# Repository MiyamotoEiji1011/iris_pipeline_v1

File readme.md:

# iris pipeline v1
空調設備管理デバイス
各空調機（エアコン）の温度を計測し、空調設備の電力効率向上を目的として、必要に応じてミストを噴射し、銅管温度を低下させるデバイスです。
温度センサから取得した測定値をもとに電磁弁を自動制御し、設定された温度条件に応じてミストの噴射・停止を行います。

※温度センサについて
各空調機に2台のセンサを使用する。
銅管と空気の吸気部分の2か所に配置して温度を測定する。
電磁弁の制御に使用する値はwebアプリ側で切り替えれるようにする。

# 配線
## 温度センサ(DS18B20)
GPIO04=sensor_A1,sensor_A2
GPIO05=sensor_B1,sensor_B2
GPIO06=sensor_C1,sensor_C2

GPIO12=sensor_D1,sensor_D2
GPIO13=sensor_E1,sensor_E2
GPIO16=sensor_F1,sensor_F2

GPIO17=sensor_G1,sensor_G2
GPIO18=sensor_H1,sensor_H2
GPIO19=sensor_I1,sensor_I2

GPIO20=sensor_J1,sensor_J2
GPIO21=sensor_K1,sensor_K2
GPIO26=sensor_L1,sensor_L2
## 電磁バルブ(12V)
リレーモジュールに接続(8つ)
## リレーモジュール(リレー*8)
GPIO07=relay_A
GPIO08=relay_B
GPIO09=relay_C
GPIO10=relay_D
GPIO11=relay_E
GPIO22=relay_F
GPIO23=relay_G
GPIO24=relay_H
## LED
GPIO25=DAEMON_LED
GPIO27=API_LED
GPIO14=NETWORK_LED
## SW
GPIO15=Reset_SW

# webアプリ
githubPagesをもちいて、ラズパイ側のッデータの受け取りや設定の書き換えなどを行う。APIを使用してユーザーが任意のタイミングでリクエストができるようにする。常時通信は行わない。

# コード
## main
tools,systemを使用して制御を行う。

## tools
・read_temp_sensor.py
read_temp_sensor(GPIO)->list(float)
任意のGPIOの温度センサーの値を取得可能できる数取得し返す。
・write_relay_module.py
write_relay_module(GPIO,bool)->bool()
リレーモジュールのGPIOのHIGH/LOWを切り替える
・write_temp_date.py
write_temp_date()->xlsx
指定の形式で温度データを渡すことでエクセルファイル追加保存する。また、エクセルファイルの新規作成などの関数もある。
・write_log.py
write_log()->txt
各、処理のログなどをすべて時間とともに保存する。
最大1000行までのログを記載し、超える場合は古い記録と入れ替える。

## api
未定

## system
・read_network.py
ネットワーク接続状態を確認する。
・read_api.py
外部アプリからの接続や編集を管理
・read_reset_switch.py
デーモンを終了し、システムを再起動
・read_system.py
OSの状態を管理

## config
・attach_pin.json
各GPIOのピン設定などを名前付けして定義づける。main.pyは起動時にこのファイルから読み込んだPINを使用して制御を行う。また、温度センサーの識別IDも記載。
・date_config.json
データの読み取り間隔などデータの記録に関する定義を保存するファイル。
・process_config.json
各電磁弁の開閉温度の設定、各空調機の制御で銅管温度と吸気温度のどちらを設定しているのかを保存しているファイル。
・config
　githubなどのアカウント関係に紐づく値を管理

# raspi
cd ~/iris_pipeline_v1/raspi
git pull
source .venv/bin/activate
pip install -r requirements.txt

## git
cd ~/iris_pipeline_v1
git add .
git commit -m "update raspi code"
git push

## デーモン（systemd）

### 初回登録
```bash
sudo cp ~/iris_pipeline_v1/raspi/iris_pipeline.service /etc/systemd/system/
sudo systemctl daemon-reload
sudo systemctl enable iris_pipeline
sudo systemctl start iris_pipeline
```

### 状態確認
```bash
sudo systemctl status iris_pipeline
```

### ログ確認
```bash
journalctl -u iris_pipeline -f
```

### 停止 / 起動 / 再起動
```bash
sudo systemctl stop iris_pipeline
sudo systemctl start iris_pipeline
sudo systemctl restart iris_pipeline
```

### 自動起動の無効化
```bash
sudo systemctl disable iris_pipeline
```

### コード更新後の反映手順
```bash
cd ~/iris_pipeline_v1
git pull
sudo systemctl restart iris_pipeline
```

## システム監視デーモン（iris_system）

ネットワーク状態 LED と リセット SW を管理する独立デーモン。

### sudo reboot の許可設定（初回のみ）
```bash
sudo visudo
```
以下の行を末尾に追加して保存：
```
pi ALL=(ALL) NOPASSWD: /sbin/reboot
```

### 初回登録
```bash
sudo cp ~/iris_pipeline_v1/raspi/iris_system.service /etc/systemd/system/
sudo systemctl daemon-reload
sudo systemctl enable iris_system
sudo systemctl start iris_system
```

### 状態確認 / ログ
```bash
sudo systemctl status iris_system
journalctl -u iris_system -f
```

### 停止 / 起動 / 再起動
```bash
sudo systemctl stop iris_system
sudo systemctl start iris_system
sudo systemctl restart iris_system
```

### コード更新後の反映手順
```bash
cd ~/iris_pipeline_v1
git pull
sudo systemctl restart iris_system
```

# webapp
https://miyamotoeiji1011.github.io/iris_pipeline_v1/

# Tailscale
IPの確認
tailscale ip -4

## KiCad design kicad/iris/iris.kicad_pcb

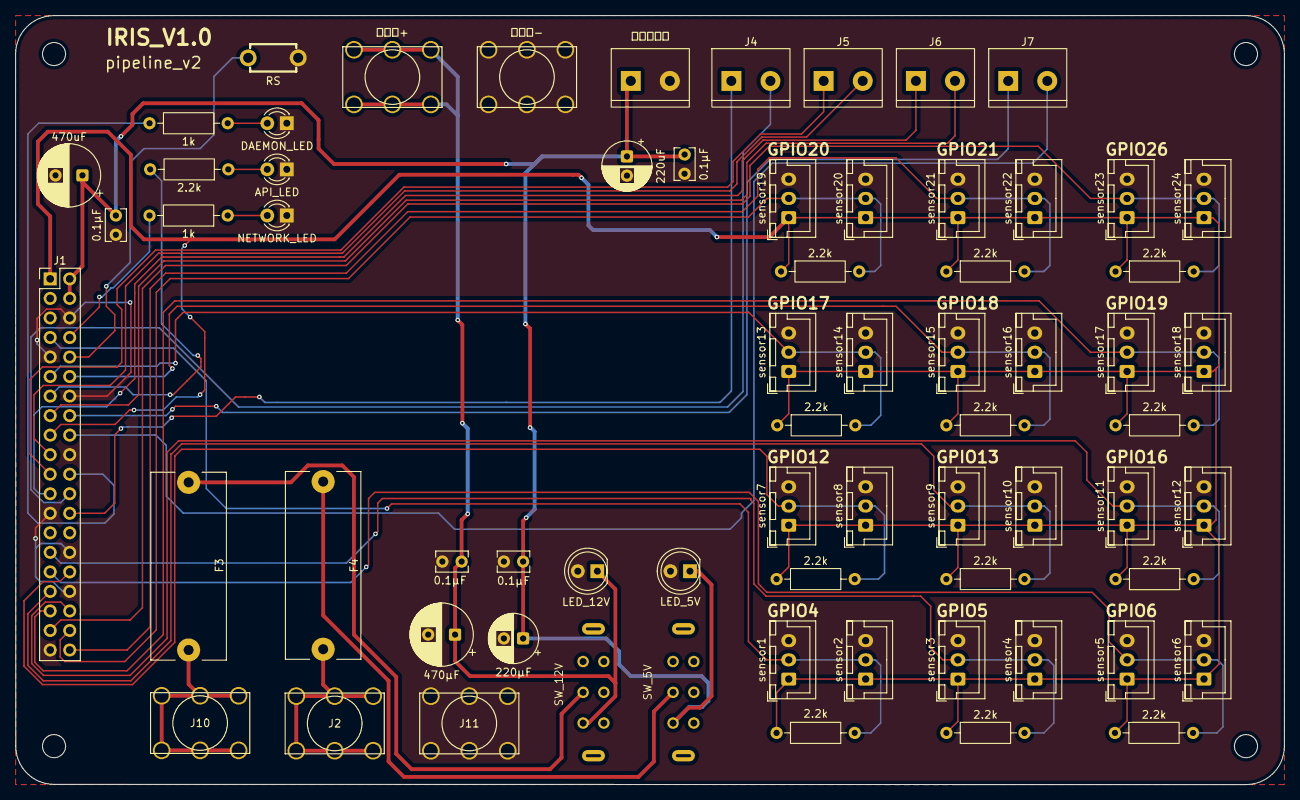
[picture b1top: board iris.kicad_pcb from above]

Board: 2 copper layers, 165.0 x 100.0 mm, 68 parts (0 on the bottom side), 35 nets.

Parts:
0.1µF, 0.1µF#2, 0.1µF#3, 0.1µF#4: 0.1µF; C_Rect_L4.0mm_W2.5mm_P2.50mm
1k, 1k#2: 1k; R_Axial_DIN0207_L6.3mm_D2.5mm_P10.16mm_Horizontal
2.2k, 2.2k#2, 2.2k#3, 2.2k#4, 2.2k#5, 2.2k#6, 2.2k#7, 2.2k#8, 2.2k#9, 2.2k#10, 2.2k#11, 2.2k#12, 2.2k#13: 2.2k; R_Axial_DIN0207_L6.3mm_D2.5mm_P10.16mm_Horizontal
220uF: 220uF; CP_Radial_D6.3mm_P2.50mm
220µF: 220µF; CP_Radial_D6.3mm_P2.50mm
470uF: 470uF; CP_Radial_D8.0mm_P3.50mm
470µF: 470µF; CP_Radial_D8.0mm_P3.50mm
API_LED: API_LED; LED_D3.0mm
DAEMON_LED: DAEMON_LED; LED_D3.0mm
F3, F4: Fuse; Fuseholder_Cylinder-5x20mm_MF-563
J1: Conn_02x20_Odd_Even; PinHeader_2x20_P2.54mm_Vertical
J2: 電源5V; PCB-20(632)F
J4, J5, J6, J7: 信号ターミナル; TerminalBlock_Alphaplus_TB111-2-2-E-1-1_1x02_P5.08_Horizont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
J10: 電源12V; PCB-20(632)F
J11: 電源GND; PCB-20(632)F
LED_5V: OSG8NU5B64A-5V; LED_D5.0mm
LED_12V: OSG8NU5B64A-12V; LED_D5.0mm
NETWORK_LED: NETWORK_LED; LED_D3.0mm
RS: SW_Push; sw_TVBP06-B043CB-B
SW_5V, SW_12V: SW_DPDT_x2; SS22F06G5-G
sensor1, sensor2, sensor3, sensor4, sensor5, sensor6, sensor7, sensor8, sensor9, sensor10, sensor11, sensor12, sensor13, sensor14, sensor15, sensor16, sensor17, sensor18, sensor19, sensor20, sensor21, sensor22, sensor23, sensor24: B3B-XH-A(LF)(SN); JST_XH_B3B-XH-A_1x03_P2.50mm_Vertical
リレー電源: リレー電源ターミナル; TerminalBlock_Alphaplus_TB111-2-2-E-1-1_1x02_P5.08_Horizont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
電磁弁+: 電磁弁+; PCB-20(632)F
電磁弁-: 電磁弁-; PCB-20(632)F

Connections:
+3V3: 2.2k.1, 2.2k#2.1, 2.2k#3.1, 2.2k#4.1, 2.2k#6.1, 2.2k#7.1, 2.2k#8.1, 2.2k#9.1, 2.2k#10.1, 2.2k#11.1, 2.2k#12.1, 2.2k#13.1, J1.1, J1.17, sensor1.1, sensor2.1, sensor3.1, sensor4.1, sensor5.1, sensor6.1, sensor7.1, sensor8.1, sensor9.1, sensor10.1, sensor11.1, sensor12.1, sensor13.1, sensor14.1, sensor15.1, sensor16.1, sensor17.1, sensor18.1, sensor19.1, sensor20.1, sensor21.1, sensor22.1, sensor23.1, sensor24.1
+5V: 0.1µF#2.1, 0.1µF#3.1, 0.1µF#4.1, 220uF.1, 220µF.1, 470uF.1, J1.2, J1.4, LED_5V.1 (K), SW_5V.1 (A), リレー電源.1
+12V: 0.1µF.1, 470µF.1, LED_12V.1 (K), SW_12V.1 (A), 電磁弁+.1
GND: 0.1µF.2, 0.1µF#2.2, 0.1µF#3.2, 0.1µF#4.2, 220uF.2, 220µF.2, 470uF.2, 470µF.2, API_LED.1 (K), DAEMON_LED.1 (K), J1.6, J1.9, J1.14, J1.20, J1.25, J1.30, J1.34, J1.39, J11.1, LED_5V.2 (A), LED_12V.2 (A), NETWORK_LED.1 (K), RS.2, sensor1.3, sensor2.3, sensor3.3, sensor4.3, sensor5.3, sensor6.3, sensor7.3, sensor8.3, sensor9.3, sensor10.3, sensor11.3, sensor12.3, sensor13.3, sensor14.3, sensor15.3, sensor16.3, sensor17.3, sensor18.3, sensor19.3, sensor20.3, sensor21.3, sensor22.3, sensor23.3, sensor24.3, リレー電源.2, 電磁弁-.1
GPIO4: 2.2k#9.2, J1.7, sensor1.2, sensor2.2
GPIO5: 2.2k.2, J1.29, sensor3.2, sensor4.2
GPIO6: 2.2k#12.2, J1.31, sensor5.2, sensor6.2
GPIO7: J1.26, J4.1
GPIO8: J1.24, J4.2
GPIO9: J1.21, J5.1
GPIO10: J1.19, J5.2
GPIO11: J1.23, J6.1
GPIO12: 2.2k#7.2, J1.32, sensor7.2, sensor8.2
GPIO13: 2.2k#2.2, J1.33, sensor9.2, sensor10.2
GPIO14: 1k#2.2, J1.8
GPIO16: 2.2k#4.2, J1.36, sensor11.2, sensor12.2
GPIO17: 2.2k#11.2, J1.11, sensor13.2, sensor14.2
GPIO18: 2.2k#6.2, J1.12, sensor15.2, sensor16.2
GPIO19: 2.2k#10.2, J1.35, sensor17.2, sensor18.2
GPIO20: 2.2k#8.2, J1.38, sensor19.2, sensor20.2
GPIO21: 2.2k#3.2, J1.40, sensor21.2, sensor22.2
GPIO22: J1.15, J6.2
GPIO23: J1.16, J7.1
GPIO24: J1.18, J7.2
GPIO25: 1k.2, J1.22
GPIO26: 2.2k#13.2, J1.37, sensor23.2, sensor24.2
GPIO27: 2.2k#5.2, J1.13
unnamed: 1k.1, DAEMON_LED.2 (A)
unnamed: 2.2k#5.1, API_LED.2 (A)
unnamed: 1k#2.1, NETWORK_LED.2 (A)
unnamed: J1.10, RS.1
unnamed: F4.1, J2.1
unnamed: F3.1, J10.1
unnamed: F4.2, SW_5V.2 (B)
unnamed: F3.2, SW_12V.2 (B)
